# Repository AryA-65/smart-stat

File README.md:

# smart-stat
Smart thermostat and bluetooth temperature sensors

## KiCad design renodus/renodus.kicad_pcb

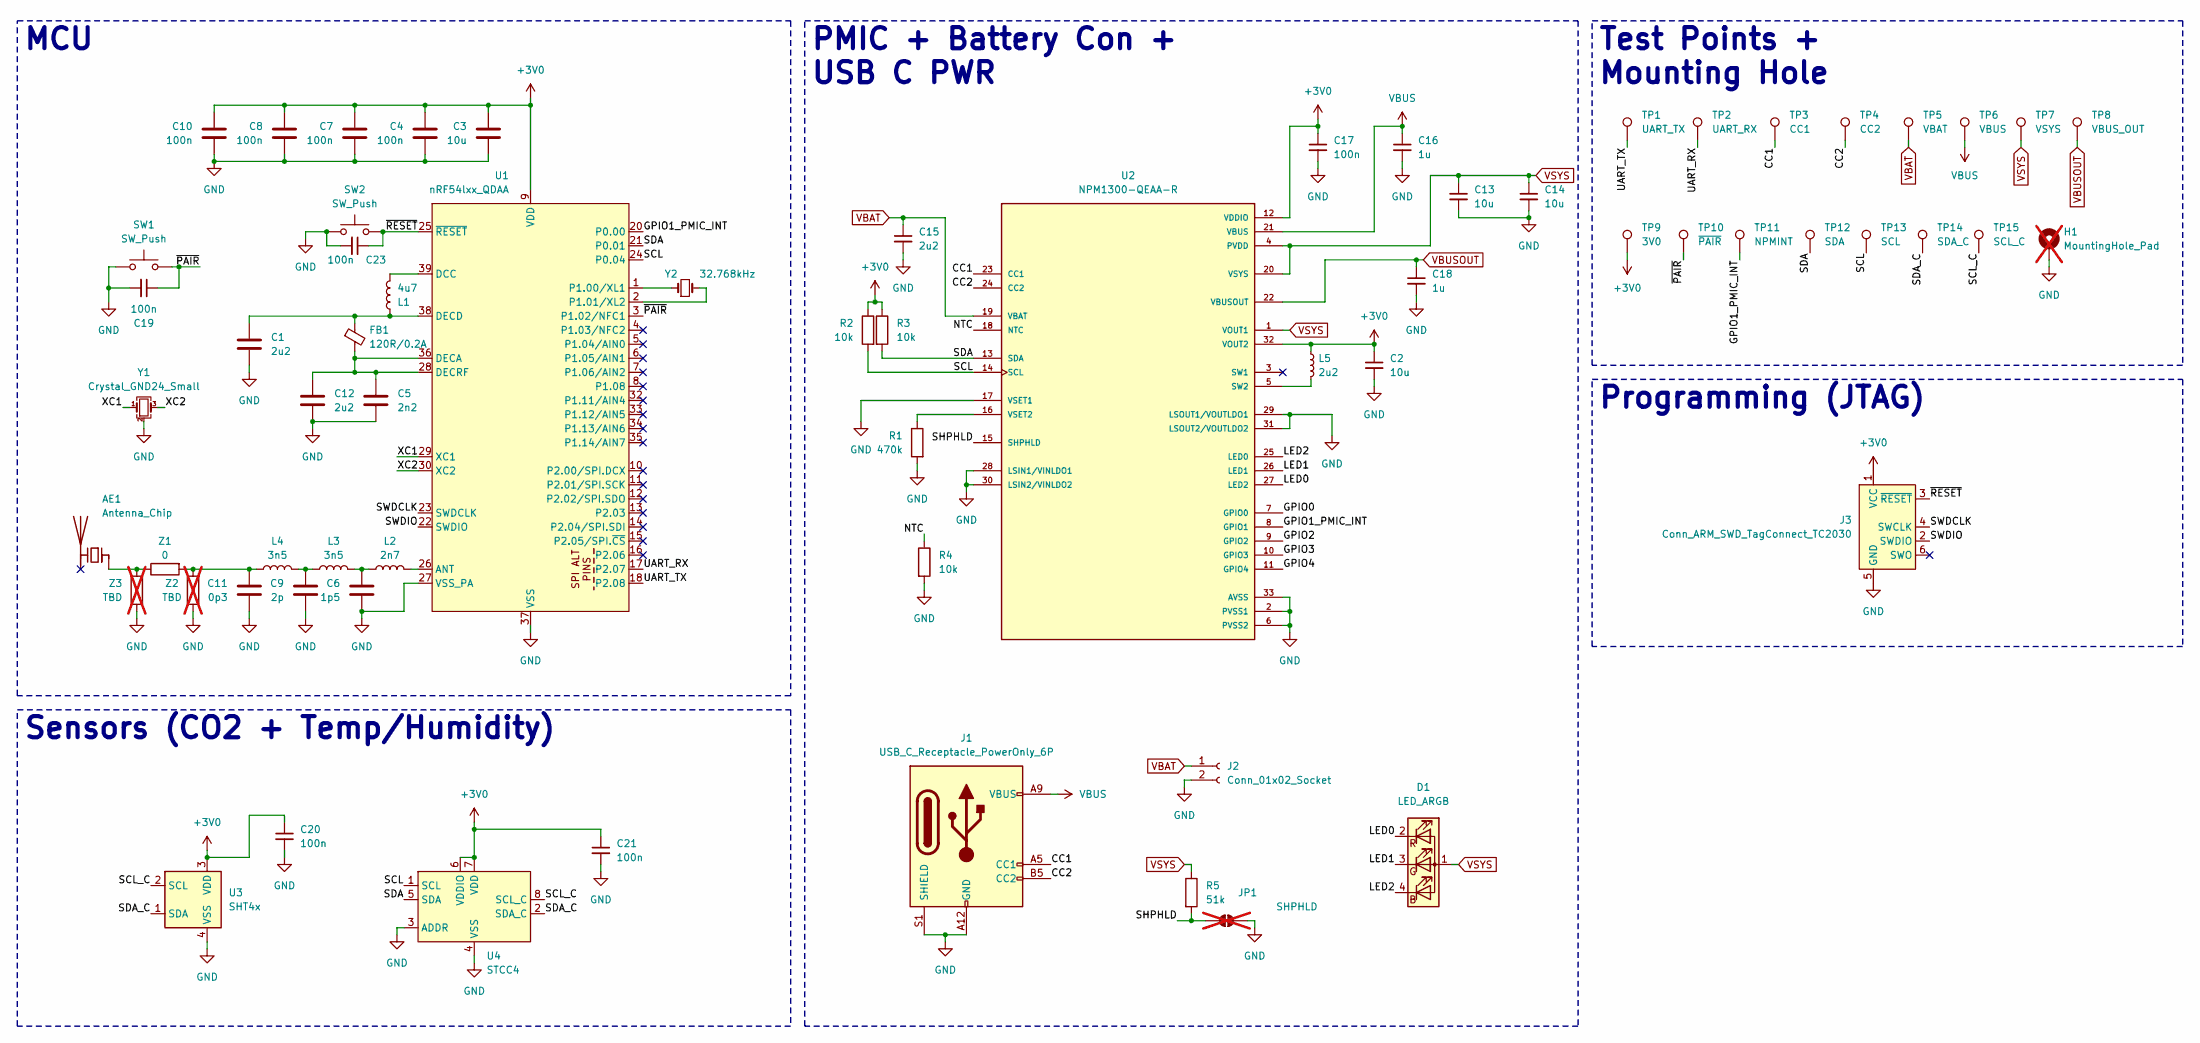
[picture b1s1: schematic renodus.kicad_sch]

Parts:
AE1: Antenna_Chip; AANI-CH-0129-T; Part Num. AANI-CH-0129-T
C1, C12: 2u2; 0201_universal; Part Num. GRM033R61A225KE47
C2, C13, C14: 10u; 0603_universal; Part Num. GRM188R61A106ME69J
C3: 10u; 0402_universal; Part Num. GRT155C80J106ME13J
C4, C7, C8, C10: 100n; 0201_universal; Part Num. GRM033Z71A104KE14D
C5: 2n2; 0201_universal; Part Num. GRM033R71A222KA01D
C6: 1p5; 0201_universal; Part Num. GJM0335C1E1R5WB01
C9: 2p; 0201_universal; Part Num. GJM0335C1E2R0WB01
C11: 0p3; 0201_universal; Part Num. GRM0335C1HR30BA01
C15: 2u2; 0603_universal; Part Num. GRM188R61E225KA12D
C16, C18: 1u; 0603_universal; Part Num. CL10A105KP8NNNC
C17, C19, C20, C21, C23: 100n; 0201_universal; Part Num. C0603X5R1E104K030BB
D1: LED_ARGB; LED_Wurth_150044M155260; Part Num. 150044M155260
FB1: 120R/0.2A; 0201_universal; Part Num. BLM03AG121SN1D
H1: MountingHole_Pad; MountingHole_2.2mm_M2_Pad_Via; not fitted
J1: USB_C_Receptacle_PowerOnly_6P; USB_C_Receptacle_GCT_USB4125-xx-x-0190_6P_TopMnt_Horizontal; Part Num. USB4125-GF-A
J2: Conn_01x02_Socket; JST_S2B-PH-SM4-TB; Part Num. S2B-PH-SM4-TB
J3: Conn_ARM_SWD_TagConnect_TC2030; Tag-Connect_TC2030-IDC-NL_2x03_P1.27mm_Vertical
JP1: SHPHLD; SolderJumper-2_P1.3mm_Open_RoundedPad1.0x1.5mm; not fitted
L1: 4u7; 0603_universal; Part Num. MLZ1608M4R7WT000
L2: 2n7; 0201_universal; Part Num. LQP03HQ2N7B02
L3, L4: 3n5; 0201_universal; Part Num. LQP03HQ3N5B02
L5: 2u2; INDC2016X100N; Part Num. CIGT201610EH2R2MNE
R1: 470k; 0201_universal; Part Num. ERJ-1GNF4703C
R2, R3, R4: 10k; 0201_universal; Part Num. RC0201FR-0710KL
R5: 51k; 0201_universal; Part Num. RC0201JR-0751KL
SW1: SW_Push; SW_SPST_Omron_B3FS-101xP; Part Num. B3FS-1012P
SW2: SW_Push; SW_Push_1P1T_NO_CK_KMR2; Part Num. KMR231G LFS
TP1: UART_TX; TestPoint_Pad_D1.0mm
TP2: UART_RX; TestPoint_Pad_D1.0mm
TP3: CC1; TestPoint_Pad_D0.5mm
TP4: CC2; TestPoint_Pad_D0.5mm
TP5: VBAT; TestPoint_Pad_D0.5mm
TP6: VBUS; TestPoint_Pad_D0.5mm
TP7: VSYS; TestPoint_Pad_D0.5mm
TP8: VBUS_OUT; TestPoint_Pad_D0.5mm
TP9: 3V0; TestPoint_Pad_D0.5mm
TP10: ~{PAIR}; TestPoint_Pad_D0.5mm
TP11: NPMINT; TestPoint_Pad_D0.5mm
TP12: SDA; TestPoint_Pad_D0.5mm
TP13: SCL; TestPoint_Pad_D0.5mm
TP14: SDA_C; TestPoint_Pad_D0.5mm
TP15: SCL_C; TestPoint_Pad_D0.5mm
U1: nRF54lxx_QDAA; QFN-40-1EP_5x5mm_P0.4mm_EP3.6x3.6mm_ThermalVias; Part Num. NRF54L10-QDAA-R7
U2: NPM1300-QEAA-R; QFN32_5X5_NOR-L; PARTREV v1.1
U3: SHT4x; Sensirion_DFN-4_1.5x1.5mm_P0.8mm_SHT4x_NoCentralPad; Part Num. SHT41A-AW1B-R3
U4: STCC4; Part Num. STCC4-D-R3
Y1: Crystal_GND24_Small; Crystal_SMD_2016-4Pin_2.0x1.6mm; Part Num. CX2016DB32000D0WZRC1
Y2: 32.768kHz; Crystal_SMD_2012-2Pin_2.0x1.2mm; Part Num. 9HT11-32.768KDZC-T
Z1: 0; 0201_universal; Part Num. RC0201JR-070RL
Z2, Z3: TBD; 0201_universal; not fitted

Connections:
+3V0: C2.1, C3.1, C4.1, C7.1, C8.1, C10.1, C17.1, C20.1, C21.1, J3.1 (VCC), L5.1, R2.1, R3.1, TP9.1 (1_1), U1.9 (VDD), U1.19 (VDD), U1.31 (VDD), U1.40 (VDD), U2.12 (VDDIO), U2.32 (VOUT2), U3.3 (VDD), U4.6 (VDDIO), U4.7 (VDD)
/CC1: J1.A5 (CC1), TP3.1 (1_1), U2.23 (CC1)
/CC2: J1.B5 (CC2), TP4.1 (1_1), U2.24 (CC2)
/GPIO0: U2.7 (GPIO0)
/GPIO1_PMIC_INT: TP11.1 (1_1), U1.20 (P0.00), U2.8 (GPIO1)
/GPIO2: U2.9 (GPIO2)
/GPIO3: U2.10 (GPIO3)
/GPIO4: U2.11 (GPIO4)
/LED0: D1.2 (RK), U2.27 (LED2)
/LED1: D1.3 (GK), U2.26 (LED1)
/LED2: D1.4 (BK), U2.25 (LED0)
/NTC: R4.1, U2.18 (NTC)
/SCL: R2.2, TP13.1 (1_1), U1.24 (P0.04), U2.14 (SCL), U4.1 (SCL)
/SCL_C: TP15.1 (1_1), U3.2 (SCL), U4.8 (SCL_C)
/SDA: R3.2, TP12.1 (1_1), U1.21 (P0.01), U2.13 (SDA), U4.5 (SDA)
/SDA_C: TP14.1 (1_1), U3.1 (SDA), U4.2 (SDA_C)
/SHPHLD: JP1.1 (A), R5.2, U2.15 (SHPHLD)
/SWDCLK: J3.4 (SWCLK), U1.23 (SWDCLK)
/SWDIO: J3.2 (SWDIO), U1.22 (SWDIO)
/UART_RX: TP2.1 (1_1), U1.17 (P2.07)
/UART_TX: TP1.1 (1_1), U1.18 (P2.08)
/XC1: U1.29 (XC1), Y1.1
/XC2: U1.30 (XC2), Y1.3
/~PAIR: C19.1, SW1.2, TP10.1 (1_1), U1.3 (P1.02/NFC1)
/~RESET: C23.1, J3.3 (~RESET), SW2.2, U1.25 (~RESET)
GND: C1.2, C2.2, C3.2, C4.2, C5.2, C6.2, C7.2, C8.2, C9.2, C10.2, C11.2, C12.2, C13.2, C14.2, C15.2, C16.2, C17.2, C18.2, C19.2, C20.2, C21.2, C23.2, H1.1 (1_1), J1.A12 (GND), J1.B12 (GND), J1.S1 (SHIELD), J2.2, J3.5 (GND), JP1.2 (B), R1.2, R4.2, SW1.1, SW2.1, U1.27 (VSS_PA), U1.37 (VSS), U1.41 (VSS), U2.2 (PVSS1), U2.6 (PVSS2), U2.17 (VSET1), U2.28 (LSIN1/VINLDO1), U2.29 (LSOUT1/VOUTLDO1), U2.30 (LSIN2/VINLDO2), U2.31 (LSOUT2/VOUTLDO2), U2.33 (AVSS), U3.4 (VSS), U4.3 (ADDR), U4.4 (VSS), Y1.2 (G), Y1.4 (G), Z2.1, Z3.2
unnamed: AE1.1 (FEED_1), Z1.1, Z3.1
unnamed: C6.1, L2.1, L3.2
unnamed: C9.1, L3.1, L4.2
unnamed: C11.1, L4.1, Z1.2, Z2.2
unnamed: L2.2, U1.26 (ANT)
unnamed: L1.1, U1.39 (DCC)
unnamed: C5.1, C12.1, FB1.2, U1.28 (DECRF), U1.36 (DECA)
unnamed: C1.1, FB1.1, L1.2, U1.38 (DECD)
unnamed: U1.1 (P1.00/XL1), Y2.1
unnamed: U1.2 (P1.01/XL2), Y2.2
unnamed: L5.2, U2.5 (SW2)
unnamed: R1.1, U2.16 (VSET2)
VBAT: C15.1, J2.1, TP5.1 (1_1), U2.19 (VBAT)
VBUS: C16.1, J1.A9 (VBUS), J1.B9 (VBUS), TP6.1 (1_1), U2.21 (VBUS)
VBUSOUT: C18.1, TP8.1 (1_1), U2.22 (VBUSOUT)
VSYS: C13.1, C14.1, D1.1 (A), R5.1, TP7.1 (1_1), U2.1 (VOUT1), U2.4 (PVDD), U2.20 (VSYS)

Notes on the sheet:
MCU
Sensors (CO2 + Temp/Humidity)
PMIC + Battery Con + USB C PWR
Test Points + Mounting Hole
Programming (JTAG)

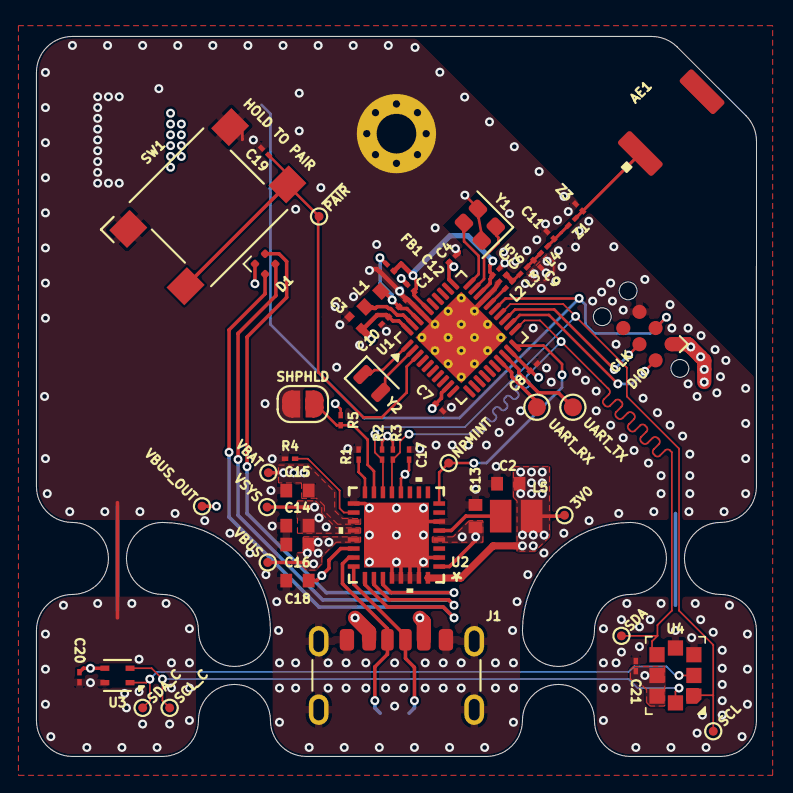
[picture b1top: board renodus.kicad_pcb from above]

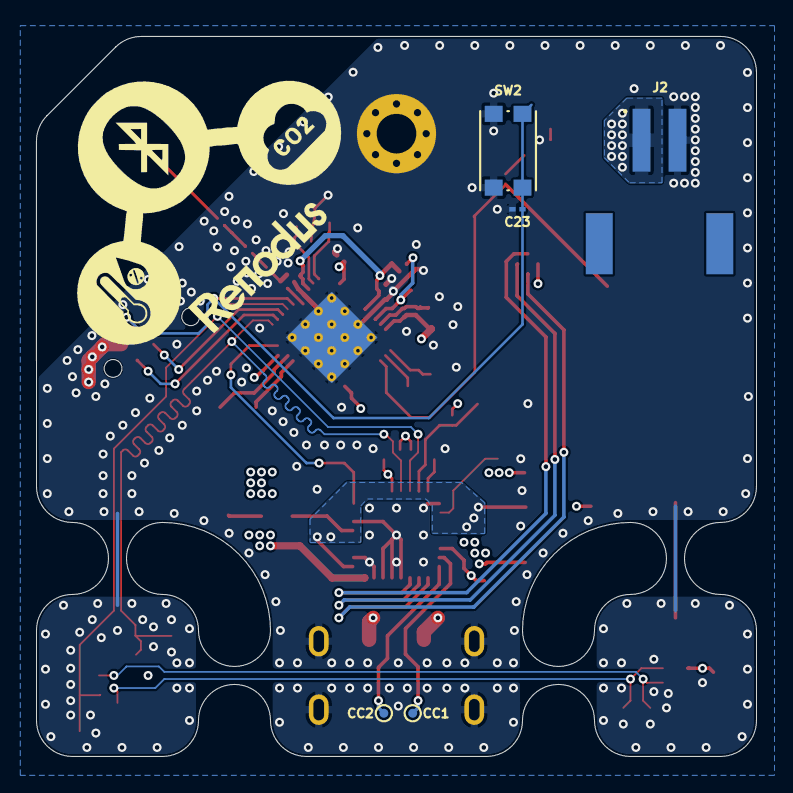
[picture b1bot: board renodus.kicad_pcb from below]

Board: 4 copper layers, 40.0 x 40.0 mm, 65 parts (5 on the bottom side), 38 nets.

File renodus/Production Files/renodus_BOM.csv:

"Reference","Qty","Value","DNP","Exclude from BOM","Exclude from Board","Footprint","Part Num.","Link"
"AE1","1","Antenna_Chip","","","","RF_Antenna:AANI-CH-0129-T","AANI-CH-0129-T","https://www.digikey.ca/en/products/detail/abracon-llc/AANI-C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"
"C1,C12","2","2u2","","","","smaller_sizes:0201_universal","GRM033R61A225KE47","https://www.digikey.ca/en/products/detail/murata-electronics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"
"C2,C13,C14","3","10u","","","","smaller_sizes:0603_universal","GRM188R61A106ME69J","https://www.digikey.ca/en/products/detail/murata-electronics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"
"C3","1","10u","","","","smaller_sizes:0402_universal","GRT155C80J106ME13J","https://www.digikey.ca/en/products/detail/murata-electronics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"
"C4,C7,C8,C10","4","100n","","","","smaller_sizes:0201_universal","GRM033Z71A104KE14D","https://www.digikey.ca/en/products/detail/murata-electronics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"
"C5","1","2n2","","","","smaller_sizes:0201_universal","GRM033R71A222KA01D","https://www.digikey.ca/en/products/detail/murata-electronics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"
"C6","1","1p5","","","","smaller_sizes:0201_universal","GJM0335C1E1R5WB01","https://www.digikey.ca/en/products/detail/murata-electronics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"
"C9","1","2p","","","","smaller_sizes:0201_universal","GJM0335C1E2R0WB01","https://www.digikey.ca/en/products/detail/murata-electronics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"
"C11","1","0p3","","","","smaller_sizes:0201_universal","GRM0335C1HR30BA01","https://www.digikey.ca/en/products/detail/murata-electronics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"
"C15","1","2u2","","","","smaller_sizes:0603_universal","GRM188R61E225KA12D","https://www.digikey.ca/en/products/detail/murata-electronics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"
"C16,C18","2","1u","","","","smaller_sizes:0603_universal","CL10A105KP8NNNC","https://www.digikey.ca/en/products/detail/samsung-electro-me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"
"C17,C19,C20,C21,C23","5","100n","","","","smaller_sizes:0201_universal","C0603X5R1E104K030BB","https://www.digikey.ca/en/products/detail/tdk/C0603X5R1E104K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"
"D1","1","LED_ARGB","","","","LED_SMD:LED_Wurth_150044M155260","150044M155260","https://www.digikey.ca/en/products/detail/w%C3%BCrth-elektro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"
"FB1","1","120R/0.2A","","","","smaller_sizes:0201_universal","BLM03AG121SN1D","https://www.digikey.ca/en/products/detail/murata-electronics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"
"J1","1","USB_C_Receptacle_PowerOnly_6P","","","","Connector_USB:USB_C_Receptacle_GCT_USB4125-xx-x-0190_6P_TopMnt_Horizontal","USB4125-GF-A","https://www.digikey.ca/en/products/detail/gct/USB4125-GF-A/13547388"
"J2","1","Conn_01x02_Socket","","","","JST_S2B-PH-SM4-TB:JST_S2B-PH-SM4-TB","S2B-PH-SM4-TB","https://www.digikey.ca/en/products/detail/jst-sales-america-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"
"L1","1","4u7","","","","smaller_sizes:0603_universal","MLZ1608M4R7WT000","https://www.digikey.ca/en/products/detail/tdk/MLZ1608M4R7WT000"
"L2","1","2n7","","","","smaller_sizes:0201_universal","LQP03HQ2N7B02","https://www.digikey.ca/en/products/detail/murata-electronics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"
"L3,L4","2","3n5","","","","smaller_sizes:0201_universal","LQP03HQ3N5B02","https://www.digikey.ca/en/products/detail/murata-electronics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"
"L5","1","2u2","","","","inductor_0806:INDC2016X100N","CIGT201610EH2R2MNE","https://www.digikey.ca/en/products/detail/samsung-electro-me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"
"R1","1","470k","","","","smaller_sizes:0201_universal","ERJ-1GNF4703C","https://www.digikey.ca/en/products/detail/panasonic-industry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"
"R2,R3,R4","3","10k","","","","smaller_sizes:0201_universal","RC0201FR-0710KL","https://www.digikey.ca/en/products/detail/yageo/RC0201FR-071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"
"R5","1","51k","","","","smaller_sizes:0201_universal","RC0201JR-0751KL","https://www.digikey.ca/en/products/detail/yageo/RC0201JR-075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"
"SW1","1","SW_Push","","","","Button_Switch_SMD:SW_SPST_Omron_B3FS-101xP","B3FS-1012P","https://www.digikey.ca/en/products/detail/aratas-america-llc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"
"SW2","1","SW_Push","","","","Button_Switch_SMD:SW_Push_1P1T_NO_CK_KMR2","KMR231G LFS","https://www.digikey.ca/en/products/detail/c-k/KMR231G-LFS/550477"
"U1","1","nRF54lxx_QDAA","","","","Package_DFN_QFN:QFN-40-1EP_5x5mm_P0.4mm_EP3.6x3.6mm_ThermalVias","NRF54L10-QDAA-R7","https://www.digikey.ca/en/products/detail/nordic-semiconduct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"
"U2","1","NPM1300-QEAA-R","","","","footprints:QFN32_5X5_NOR-L","NPM1300-QEAA-R7","https://www.digikey.ca/en/products/detail/nordic-semiconduct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"
"U3","1","SHT4x","","","","Sensor_Humidity:Sensirion_DFN-4_1.5x1.5mm_P0.8mm_SHT4x_NoCentralPad","SHT41A-AW1B-R3","https://www.digikey.ca/en/products/detail/sensirion-ag/SHT41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"
"U4","1","STCC4","","","","Sensor:STCC4","STCC4-D-R3","https://www.digikey.ca/en/products/detail/sensirion-ag/STCC4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"
"Y1","1","Crystal_GND24_Small","","","","Crystal:Crystal_SMD_2016-4Pin_2.0x1.6mm","CX2016DB32000D0WZRC1","https://www.digikey.ca/en/products/detail/kyocera-avx/CX2016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"
"Y2","1","32.768kHz","","","","Crystal:Crystal_SMD_2012-2Pin_2.0x1.2mm","9HT11-32.768KDZC-T","https://www.digikey.ca/en/products/detail/kyocera-avx/CX2016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"
"Z1","1","0","","","","smaller_sizes:0201_universal","RC0201JR-070RL","https://www.digikey.ca/en/products/detail/yageo/RC0201JR-070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"

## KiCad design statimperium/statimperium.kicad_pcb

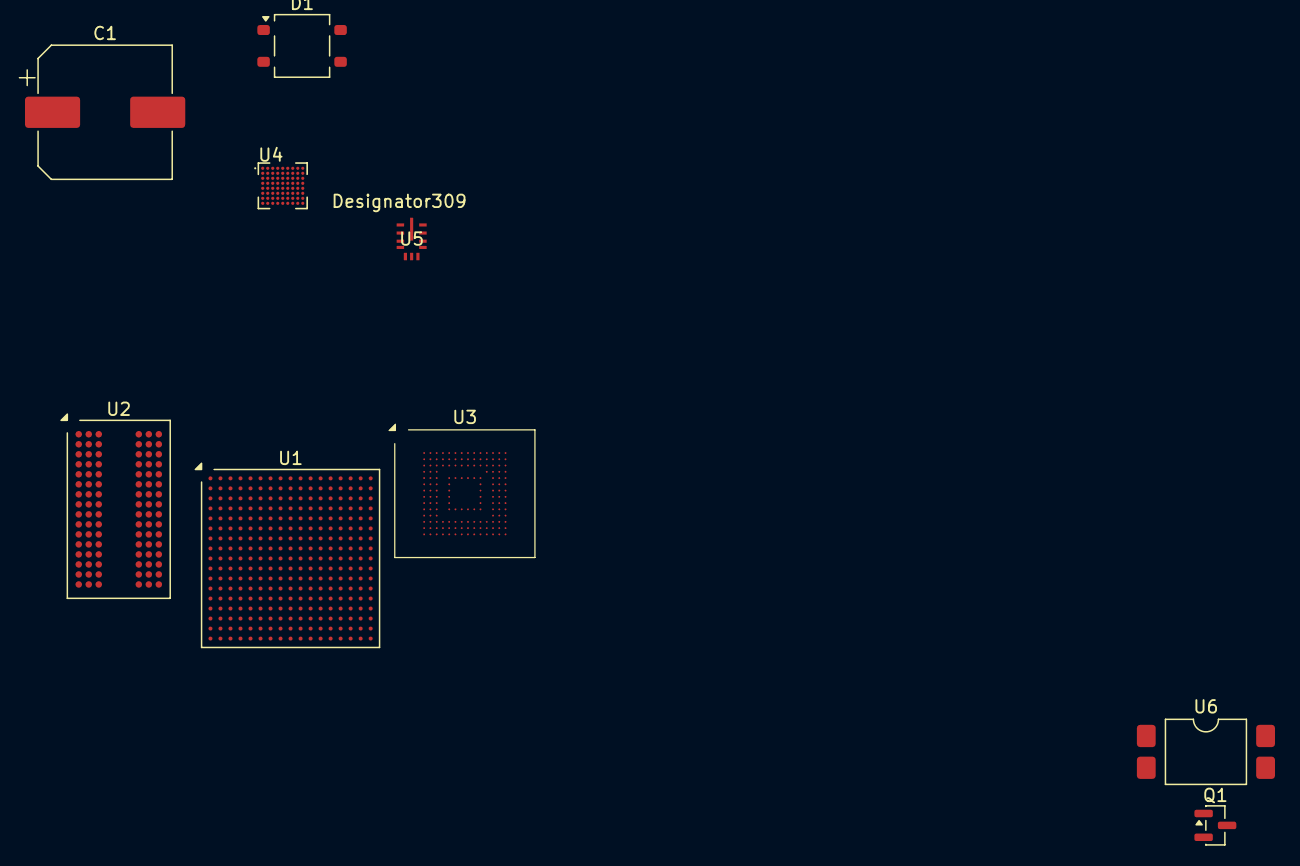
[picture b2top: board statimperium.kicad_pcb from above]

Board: 2 copper layers, 9 parts (0 on the bottom side), 48 nets, no tracks yet.

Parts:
C1: C_Polarized_US; CP_Elec_10x10.5
D1: MB6S; TO-269AA
Q1: BSS138; SOT-23
U1: STM32MP135FAEx; LFBGA-289_14x14mm_Layout17x17_P0.8mm
U2: MT41K256M16TW; Micron_FBGA-96_8x14mm_Layout9x16_P0.8mm
U3: KLM4G1FETE-B041; BGA153_11x10mm_0.15mm
U4: MAX77818EWZ_T; BGA72N40P9X8_386X360X69N
U5: LMR36015ARNXR; RNX0012B
U6: SFH617A-1X007T; SMDIP-4_W9.53mm_Clearance8mm

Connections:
/MPU/A0: U1.G16 (DDR_A0), U2.N3 (A0)
/MPU/A1: U1.K15 (DDR_A1), U2.P7 (A1)
/MPU/A2: U1.F17 (DDR_A2), U2.P3 (A2)
/MPU/A3: U1.G15 (DDR_A3), U2.N2 (A3)
/MPU/A4: U1.M14 (DDR_A4), U2.P8 (A4)
/MPU/A5: U1.E16 (DDR_A5), U2.P2 (A5)
/MPU/A6: U1.M17 (DDR_A6), U2.R8 (A6)
/MPU/A7: U1.G14 (DDR_A7), U2.R2 (A7)
/MPU/A8: U1.L15 (DDR_A8), U2.T8 (A8)
/MPU/A9: U1.F16 (DDR_A9), U2.R3 (A9)
/MPU/A10: U1.J14 (DDR_A10), U2.L7 (A10/AP)
/MPU/A11: U1.K13 (DDR_A11), U2.R7 (A11)
/MPU/A12: U1.K17 (DDR_A12), U2.N7 (A12/~BC)
/MPU/A13: U1.F14 (DDR_A13), U2.T3 (A13)
/MPU/A14: U1.L17 (DDR_A14), U2.T7 (A14)
/MPU/DQ0: U1.B17 (DDR_DQ0), U2.E3 (DQ0)
/MPU/DQ1: U1.C15 (DDR_DQ1), U2.F7 (DQ1)
/MPU/DQ2: U1.E13 (DDR_DQ2), U2.F2 (DQ2)
/MPU/DQ3: U1.D17 (DDR_DQ3), U2.F8 (DQ3)
/MPU/DQ4: U1.B16 (DDR_DQ4), U2.H3 (DQ4)
/MPU/DQ5: U1.D16 (DDR_DQ5), U2.H8 (DQ5)
/MPU/DQ6: U1.E14 (DDR_DQ6), U2.G2 (DQ6)
/MPU/DQ7: U1.E15 (DDR_DQ7), U2.H7 (DQ7)
/MPU/DQ8: U1.N16 (DDR_DQ8), U2.D7 (DQ8)
/MPU/DQ9: U1.P17 (DDR_DQ9), U2.C3 (DQ9)
/MPU/DQ10: U1.N15 (DDR_DQ10), U2.C8 (DQ10)
/MPU/DQ11: U1.P15 (DDR_DQ11), U2.C2 (DQ11)
/MPU/DQ12: U1.R15 (DDR_DQ12), U2.A7 (DQ12)
/MPU/DQ13: U1.P16 (DDR_DQ13), U2.A2 (DQ13)
/MPU/DQ14: U1.T17 (DDR_DQ14), U2.B8 (DQ14)
/MPU/DQ15: U1.T16 (DDR_DQ15), U2.A3 (DQ15)
GND: U4.A6 (GND_Q), U4.D1 (GND_A), U4.D2 (GND_A), U4.D3 (GND_A), U4.D4 (GND_A), U4.D5 (GND_A), U4.E3 (GND_D)
unnamed: U1.A1 (VSS), U1.A17 (VSS), U1.C8 (VSS), U1.D3 (VSS), U1.D12 (VSS), U1.E5 (VSS), U1.F13 (VSS), U1.F15 (VSS), U1.G7 (VSS), U1.G8 (VSS), U1.G9 (VSS), U1.G10 (VSS), U1.G11 (VSS), U1.H7 (VSS), U1.H11 (VSS), U1.H14 (VSS), U1.J7 (VSS), U1.J9 (VSS), U1.J11 (VSS), U1.K3 (VSS), U1.K7 (VSS), U1.K11 (VSS), U1.L7 (VSS), U1.L8 (VSS), U1.L9 (VSS), U1.L10 (VSS), U1.L11 (VSS), U1.M15 (VSS), U1.N4 (VSS), U1.P11 (VSS), U1.R5 (VSS), U1.R8 (VSS), U1.U1 (VSS), U1.U17 (VSS)
unnamed: U2.A1 (V_{DDQ}), U2.A8 (V_{DDQ}), U2.C1 (V_{DDQ}), U2.C9 (V_{DDQ}), U2.D2 (V_{DDQ}), U2.E9 (V_{DDQ}), U2.F1 (V_{DDQ}), U2.H2 (V_{DDQ}), U2.H9 (V_{DDQ})
unnamed: U2.B2 (V_{DD}), U2.D9 (V_{DD}), U2.G7 (V_{DD}), U2.K2 (V_{DD}), U2.K8 (V_{DD}), U2.N1 (V_{DD}), U2.N9 (V_{DD}), U2.R1 (V_{DD}), U2.R9 (V_{DD})
unnamed: U2.B1 (V_{SSQ}), U2.B9 (V_{SSQ}), U2.D1 (V_{SSQ}), U2.D8 (V_{SSQ}), U2.E2 (V_{SSQ}), U2.E8 (V_{SSQ}), U2.F9 (V_{SSQ}), U2.G1 (V_{SSQ}), U2.G9 (V_{SSQ})
unnamed: U2.A9 (V_{SS}), U2.B3 (V_{SS}), U2.E1 (V_{SS}), U2.G8 (V_{SS}), U2.J2 (V_{SS}), U2.J8 (V_{SS}), U2.M1 (V_{SS}), U2.M9 (V_{SS}), U2.P1 (V_{SS}), U2.P9 (V_{SS}), U2.T1 (V_{SS}), U2.T9 (V_{SS})
unnamed: U4.G3 (BATT), U4.G4 (BATT), U4.H3 (BATT), U4.H4 (BATT)
unnamed: U4.B8 (BYP), U4.C7 (BYP), U4.D7 (BYP), U4.E8 (BYP), U4.E9 (BYP)
unnamed: U4.C8 (CHGIN), U4.C9 (CHGIN), U4.D8 (CHGIN), U4.D9 (CHGIN)
unnamed: U4.F8 (CHGLX), U4.F9 (CHGLX), U4.G8 (CHGLX), U4.G9 (CHGLX)
unnamed: U4.H7 (CHGPG), U4.H8 (CHGPG), U4.H9 (CHGPG)
unnamed: U4.E5 (SYS), U4.F5 (SYS), U4.G5 (SYS), U4.H5 (SYS), U4.H6 (SYS)
unnamed: U4.E1 (SYS_A), U4.F2 (SYS_A)
unnamed: U4.A7 (WCIN), U4.A8 (WCIN)
VCC: U3.E6 (VCC), U3.F5 (VCC), U3.J10 (VCC)
VCCQ: U3.C6 (VCCQ), U3.M4 (VCCQ), U3.N4 (VCCQ)
VSS: U3.A6 (VSS), U3.C4 (VSS), U3.E7 (VSS), U3.G5 (VSS), U3.H10 (VSS), U3.J5 (VSS), U3.N2 (VSS), U3.N5 (VSS)

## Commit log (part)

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2026-06-08 Initial commit (testing)
2026-06-08 Replaced folder
